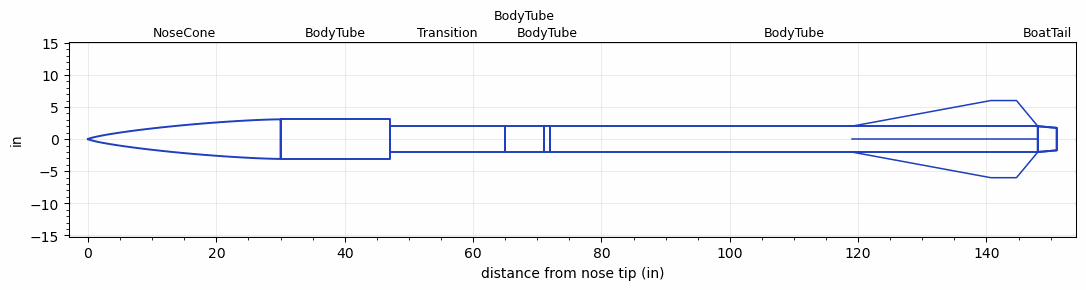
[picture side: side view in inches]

<RASAeroDocument>
 <FileVersion>2</FileVersion>
 <RocketDesign>
  <NoseCone>
   <Length>29.9999</Length>
   <Diameter>6.17</Diameter>
   <Shape>Von Karman Ogive</Shape>
   <Location>0</Location>
  </NoseCone>
  <BodyTube>
   <Length>17</Length>
   <Diameter>6.17</Diameter>
   <Location>29.9999</Location>
  </BodyTube>
  <Transition>
   <Length>18</Length>
   <Diameter>4.02</Diameter>
   <Location>46.9999</Location>
   <RearDiameter>4.02</RearDiameter>
  </Transition>
  <BodyTube>
   <Length>6</Length>
   <Diameter>4.02</Diameter>
   <Location>64.9999</Location>
  </BodyTube>
  <BodyTube>
   <Length>1</Length>
   <Diameter>4.02</Diameter>
   <Location>70.9999</Location>
  </BodyTube>
  <BodyTube>
   <Length>75.9998</Length>
   <Diameter>4.02</Diameter>
   <Location>71.9999</Location>
   <BoattailLength>2.9528</BoattailLength>
   <BoattailRearDiameter>3.5</BoattailRearDiameter>
   <Fin>
    <Count>4</Count>
    <Chord>28.9999</Chord>
    <Span>4</Span>
    <SweepDistance>21.6717</SweepDistance>
    <TipChord>4</TipChord>
    <Thickness>0.1181</Thickness>
    <Location>28.9999</Location>
    <AirfoilSection>Rounded</AirfoilSection>
   </Fin>
  </BodyTube>
  <BoatTail>
   <Length>2.9528</Length>
   <Diameter>4.02</Diameter>
   <RearDiameter>3.5</RearDiameter>
   <Location>147.9997</Location>
  </BoatTail>
  <Surface>Smooth Paint</Surface>
  <ModifiedBarrowman>False</ModifiedBarrowman>
  <Turbulence>False</Turbulence>
  <UseBooster1>False</UseBooster1>
  <UseBooster2>False</UseBooster2>
 </RocketDesign>
 <LaunchSite>
  <Altitude>4595</Altitude>
  <Pressure>30.09</Pressure>
  <RodAngle>0</RodAngle>
  <RodLength>17</RodLength>
  <Temperature>110</Temperature>
  <WindSpeed>4.47</WindSpeed>
 </LaunchSite>
 <Recovery>
  <Altitude1>656.168</Altitude1>
  <Altitude2>1000</Altitude2>
  <DeviceType1>Parachute</DeviceType1>
  <DeviceType2>Parachute</DeviceType2>
  <Event1>True</Event1>
  <Event2>True</Event2>
  <Size1>47.9999</Size1>
  <Size2>144</Size2>
  <EventType1>Apogee</EventType1>
  <EventType2>Altitude</EventType2>
  <CD1>2.2</CD1>
  <CD2>2.2</CD2>
 </Recovery>
 <SimulationList>
  <Simulation>
   <SustainerEngine>O5500X  (AT)</SustainerEngine>
   <SustainerLaunchWt>67.66</SustainerLaunchWt>
   <SustainerNozzleDiameter>3.5</SustainerNozzleDiameter>
   <SustainerCG>92.43</SustainerCG>
   <SustainerIgnitionDelay>0</SustainerIgnitionDelay>
   <Booster1SeparationDelay>0</Booster1SeparationDelay>
   <Booster1IgnitionDelay>0</Booster1IgnitionDelay>
   <IncludeBooster1>False</IncludeBooster1>
   <Booster2Delay>0</Booster2Delay>
   <IncludeBooster2>False</IncludeBooster2>
   <TimetoApogee>47.03811</TimetoApogee>
   <MaxAltitude>42248.46</MaxAltitude>
   <MaxVelocity>2419.522</MaxVelocity>
  </Simulation>
  <Simulation>
   <SustainerEngine>N3300R-P  (AT)</SustainerEngine>
   <SustainerLaunchWt>66.76</SustainerLaunchWt>
   <SustainerNozzleDiameter>3</SustainerNozzleDiameter>
   <SustainerCG>92.87</SustainerCG>
   <SustainerIgnitionDelay>0</SustainerIgnitionDelay>
   <Booster1SeparationDelay>0</Booster1SeparationDelay>
   <Booster1IgnitionDelay>0</Booster1IgnitionDelay>
   <IncludeBooster1>False</IncludeBooster1>
   <Booster2Delay>0</Booster2Delay>
   <IncludeBooster2>False</IncludeBooster2>
   <TimetoApogee>37.25975</TimetoApogee>
   <MaxAltitude>23569.91</MaxAltitude>
   <MaxVelocity>1525.463</MaxVelocity>
  </Simulation>
 </SimulationList>
</RASAeroDocument>
